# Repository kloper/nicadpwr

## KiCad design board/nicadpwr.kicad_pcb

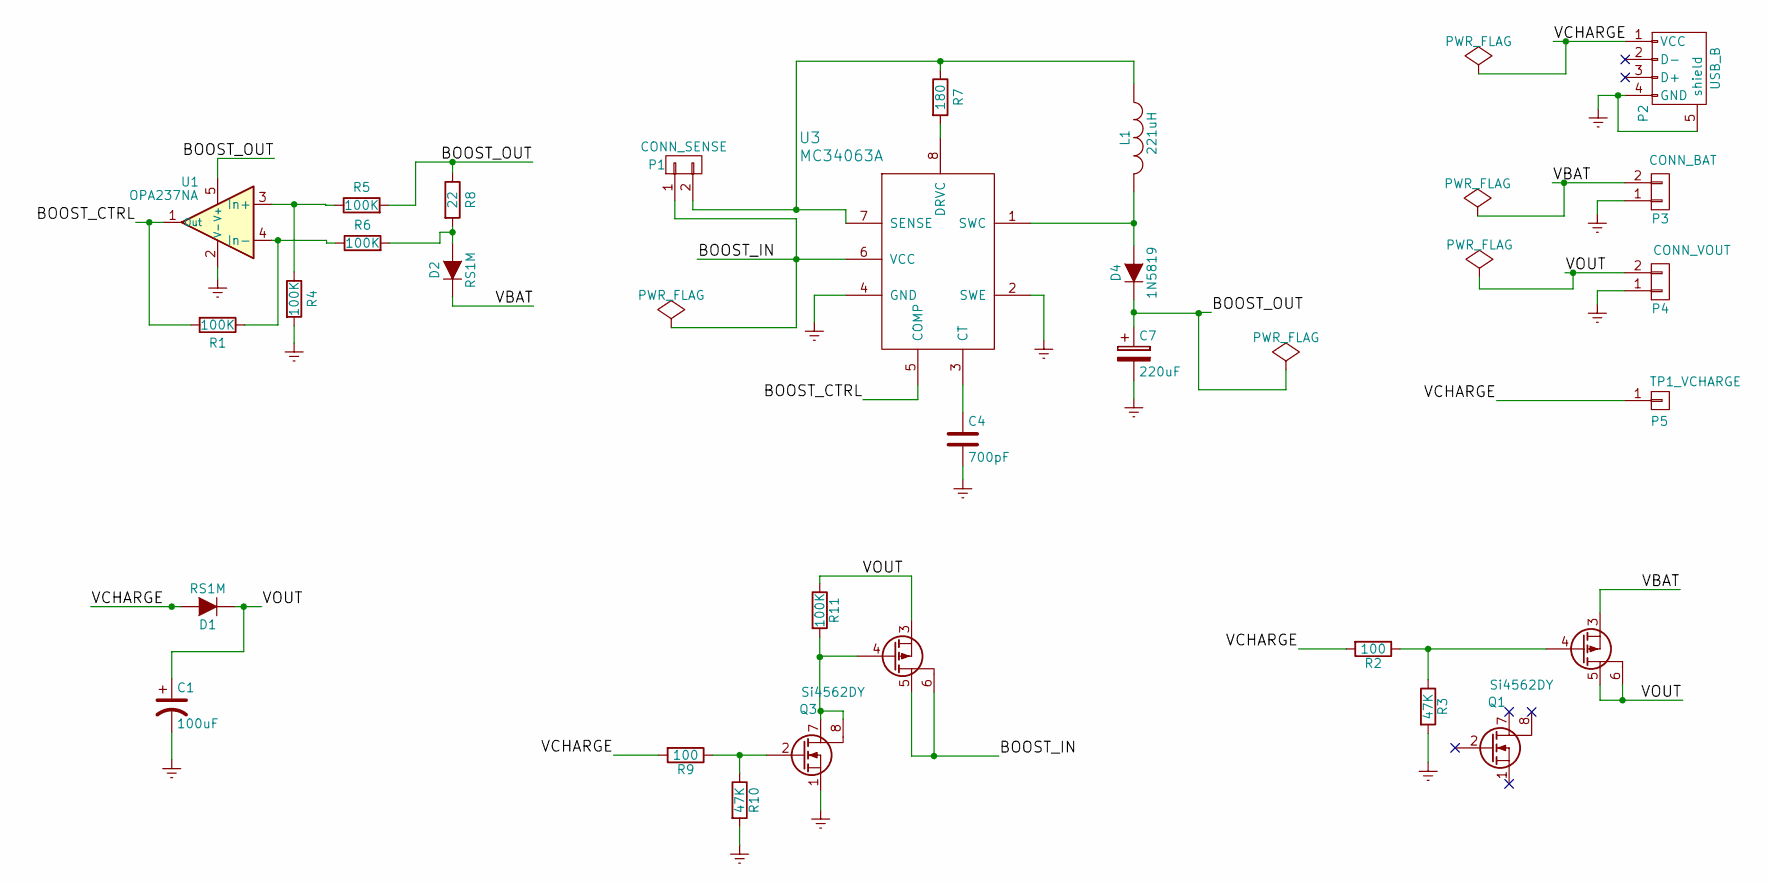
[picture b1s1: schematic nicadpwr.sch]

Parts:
C1: 100uF; CP_Tantalum_Case-U_EIA-6032-15_Hand
C4: 700pF; C_0805_HandSoldering
C7: 220uF; CP_Radial_D6.3mm_P2.50mm
D1, D2: RS1M; D_SMA_Handsoldering
D4: 1N5819; D_5W_P10.16mm_Horizontal
L1: 221uH; Inductor_Taiyo-Yuden_NR-80xx_HandSoldering
P1: CONN_SENSE; Socket_Strip_Straight_1x02_Pitch2.54mm
P2: USB_B; USB_Mini-B
P3: CONN_BAT; Socket_Strip_Straight_1x02_Pitch2.54mm
P4: CONN_VOUT; Socket_Strip_Straight_1x02_Pitch2.54mm
P5: TP1_VCHARGE; Pin_d0.9mm_L10.0mm_W2.4mm_FlatFork
Q1, Q3: Si4562DY; SOIC-8_3.9x4.9mm_Pitch1.27mm
R1, R4, R5, R6, R11: 100K; R_0805_HandSoldering
R2, R9: 100; R_0805_HandSoldering
R3, R10: 47K; R_0805_HandSoldering
R7: 180; R_0805_HandSoldering
R8: 22; R_0805_HandSoldering
U1: OPA237NA; SOT-23-5_HandSoldering
U3: MC34063A; MC34063A-DIP8

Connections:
/BOOST_CTRL: R1.2, U1.1 (Out), U3.5 (COMP)
/BOOST_IN: P1.1, Q3.5 (D2), Q3.6 (D2), U3.6 (VCC)
/BOOST_OUT: C7.1, D4.1 (K), R5.2, R8.1, U1.5 (V+)
/VBAT: D2.1 (K), P3.2, Q1.3 (S2)
/VCHARGE: D1.2 (A), P2.1 (VCC), P5.1, R2.2, R9.2
/VOUT: C1.1, D1.1 (K), P4.2, Q1.5 (D2), Q1.6 (D2), Q3.3 (S2), R11.1
Earth: C1.2, C4.2, C7.2, P2.4 (GND), P2.5 (shield), P3.1, P4.1, Q3.1 (S1), R3.2, R4.2, R10.2, U1.2 (V-), U3.2 (SWE), U3.4 (GND)
unnamed: C4.1, U3.3 (CT)
unnamed: D2.2 (A), R6.2, R8.2
unnamed: D4.2 (A), L1.2, U3.1 (SWC)
unnamed: L1.1, P1.2, R7.1, U3.7 (SENSE)
unnamed: Q1.4 (G2), R2.1, R3.1
unnamed: Q3.2 (G1), R9.1, R10.1
unnamed: Q3.4 (G2), Q3.7 (D1), Q3.8 (D1), R11.2
unnamed: R1.1, R6.1, U1.4 (In-)
unnamed: R4.1, R5.1, U1.3 (In+)
unnamed: R7.2, U3.8 (DRVC)

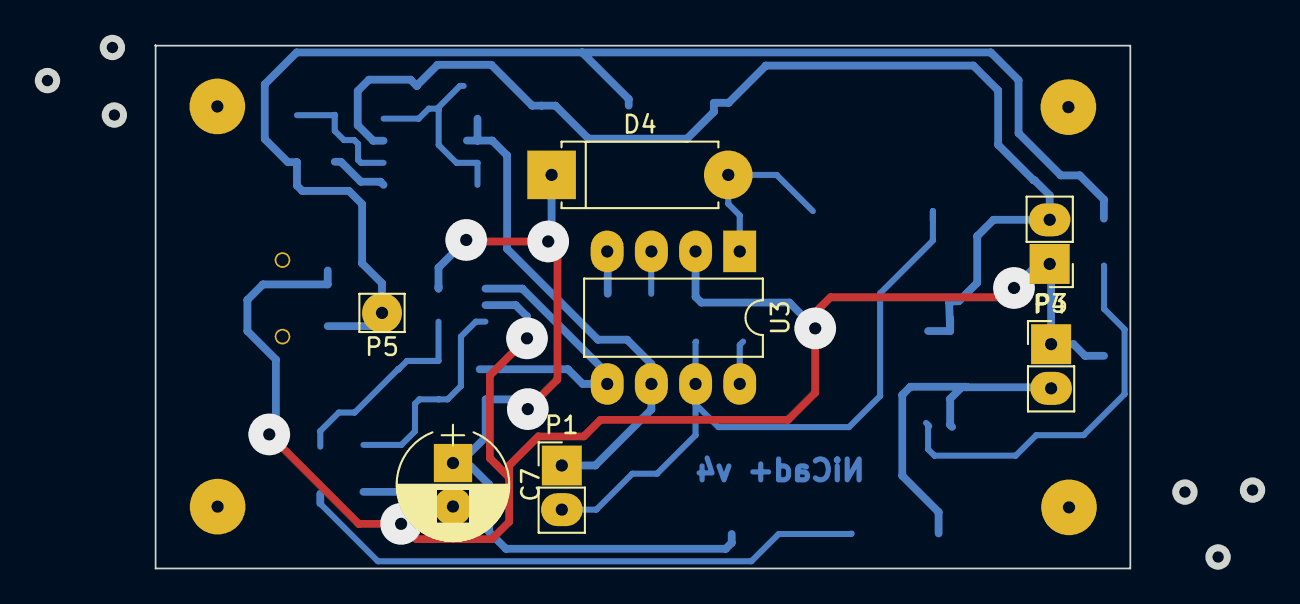
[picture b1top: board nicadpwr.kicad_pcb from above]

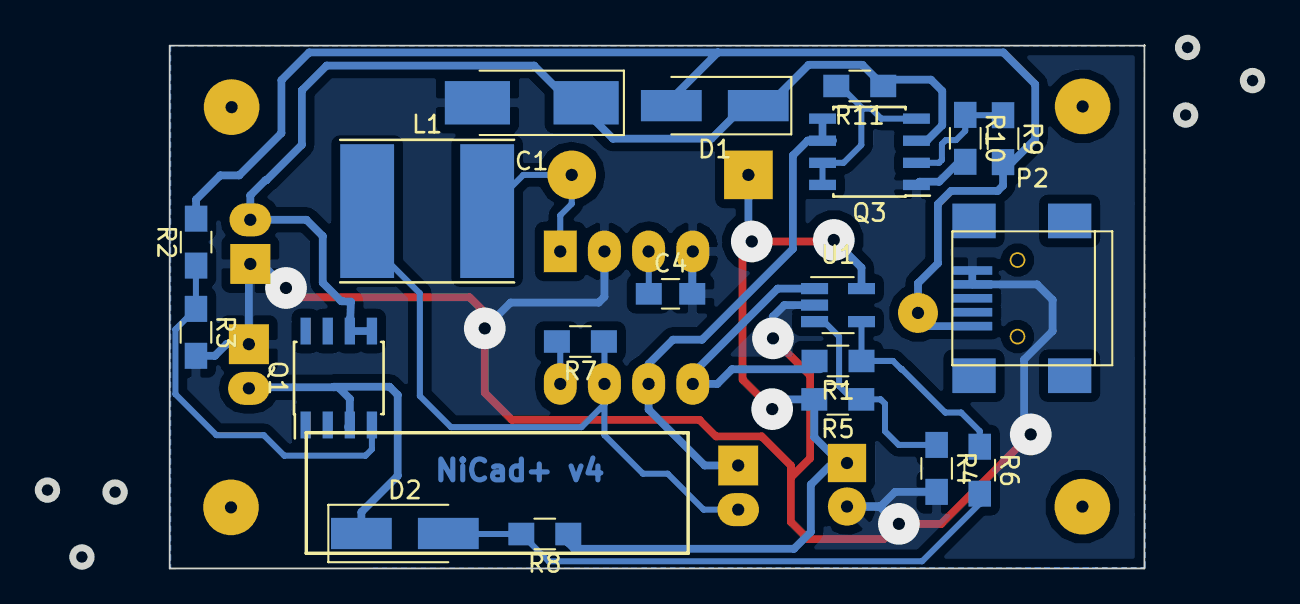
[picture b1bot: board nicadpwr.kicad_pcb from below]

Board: 2 copper layers, 70.4 x 30.4 mm, 27 parts (20 on the bottom side), 17 nets.

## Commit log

2018-01-02 Initial import of kicad project files
    NiCad is a charger and voltage step-up to 5V converter for
    battery pack of 4x 600mAH 1.2V Nickel Cadmium battery.
2018-01-10 Redesign of the board with fixes...
    1. The charging voltage is now 5V (suitable for charging from USB)
    The charging now is connected directly to boost converter and
    linear out and battery charger are connected to the boost output.
    The converter raises battery or charging voltage to 6.3 volt.
    2. Fixed problem with n-channel FET switch by using p-channel high
    side FET.
2018-01-12 Place todos on schematics before v3
2018-01-15 Minor changes
2018-01-17 Rdesign of the board for v3
    The new version moves boost converter and charger out
    of the main path to be active only when charging.
2018-01-21 Fixes in schematic only to match working version:
    1. Boost capacitor was reduced to 220uF
    2. Control signal of the VBAT-VOUT switch was changed
    to VCHARGE instead of BOOST_OUT. The problem with the
    latter is discharge time of the boost cap.
    3. Led was removed since it was not populated in the working board.
2018-02-19 Fix bugs to finaly get working board ...
    1. Upper rail for the sense opamp was set to +4V which holds its
    output under 1V. This is not enough for control of the MSP which
    is expected to be around 1.25V. Changed the upper rail to BOOST_OUT.
    2. Signal controlling Q1 battery switch was connected to BOOST_OUT.
    This works, but when charger is disconnected boost out capaccitor
    discharges relatively slowly and opens Q1 with considerable delay.
